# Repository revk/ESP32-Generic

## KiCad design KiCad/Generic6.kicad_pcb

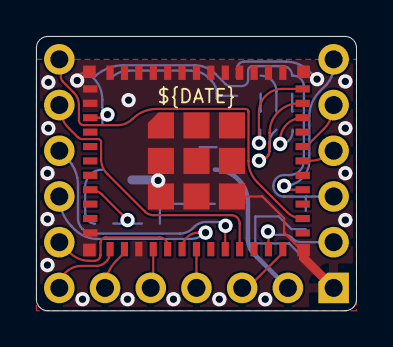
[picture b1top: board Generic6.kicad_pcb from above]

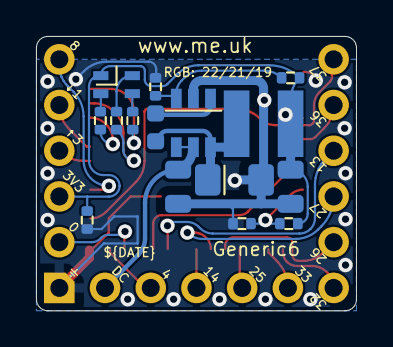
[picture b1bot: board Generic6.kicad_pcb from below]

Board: 2 copper layers, 17.8 x 15.2 mm, 29 parts (28 on the bottom side), 25 nets.

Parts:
C1: 10nF; C_0402
C2: 0.1uF; Hidden
C3: 2.2uF; Hidden
C4: 10uF; Hidden
C5: 100nF; C_0402
D1: RGB; LED-RGB-1.6x1.6
D2: Schottky; Hidden
J1: Shelly
L1: 6.8uH; Hidden
P1: 4; Round
P2: 32; Round
P3: 13; Round
P4: 25; Round
P5: 26; Round
P6: 33; Round
P7: 8; Round
P8: 27; Round
P9: 14; Round
P10: 37; Round
P11: 36; Round
P12: DC; Round
R1: 680R; R_0402
R2: 2K; R_0402
R3: 220R; R_0402
R4: 10K; R_0402
R5: 100k 1% or 0R; R_0402
R6: 30k 1% or NF; R_0402
U1: ESP32-PICO-MINI-02
U2: LMR16006+FB; RegulatorBlockFB

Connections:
+3V3: C5.1, D1.1 (A), J1.3 (3V3), R4.1, R5.1, U1.3 (3V3), U2.4 (VOUT)
B: R3.2, U1.33 (IO19)
EN: C1.2, R4.2, U1.8 (EN)
G: R2.2, U1.35 (IO21)
GND: C1.1, C5.2, J1.1 (GND), R6.1, U1.1 (GND), U1.2 (GND), U1.11 (GND), U1.14 (GND), U1.36 (GND), U1.37 (GND), U1.38 (GND), U1.39 (GND), U1.40 (GND), U1.41 (GND), U1.42 (GND), U1.43 (GND), U1.44 (GND), U1.45 (GND), U1.46 (GND), U1.47 (GND), U1.48 (GND), U1.49 (GND), U1.50 (GND), U1.51 (GND), U1.52 (GND), U1.53 (GND), U2.3 (GND)
unnamed: D1.2 (RK), R1.1
unnamed: D1.3 (GK), R2.1
unnamed: D1.4 (BK), R3.1
unnamed: J1.2 (0), U1.23 (IO0)
unnamed: J1.4 (Rx), U1.30 (RXD0)
unnamed: J1.5 (Tx), U1.31 (TXD0)
unnamed: P1.1, U1.24 (IO4)
unnamed: P2.1, U1.12 (IO32)
unnamed: P3.1, U1.20 (IO13)
unnamed: P4.1, U1.15 (IO25)
unnamed: P5.1, U1.16 (IO26)
unnamed: P6.1, U1.13 (IO33)
unnamed: P7.1, U1.28 (IO8)
unnamed: P8.1, U1.17 (IO27)
unnamed: P9.1, U1.18 (IO14)
unnamed: P12.1, U2.1 (SHDN), U2.2 (VIN)
unnamed: R5.2, R6.2, U2.5 (FB)
unnamed: P11.1, U1.21 (IO15)
unnamed: P10.1, U1.26 (IO20)
R: R1.2, U1.34 (IO22)

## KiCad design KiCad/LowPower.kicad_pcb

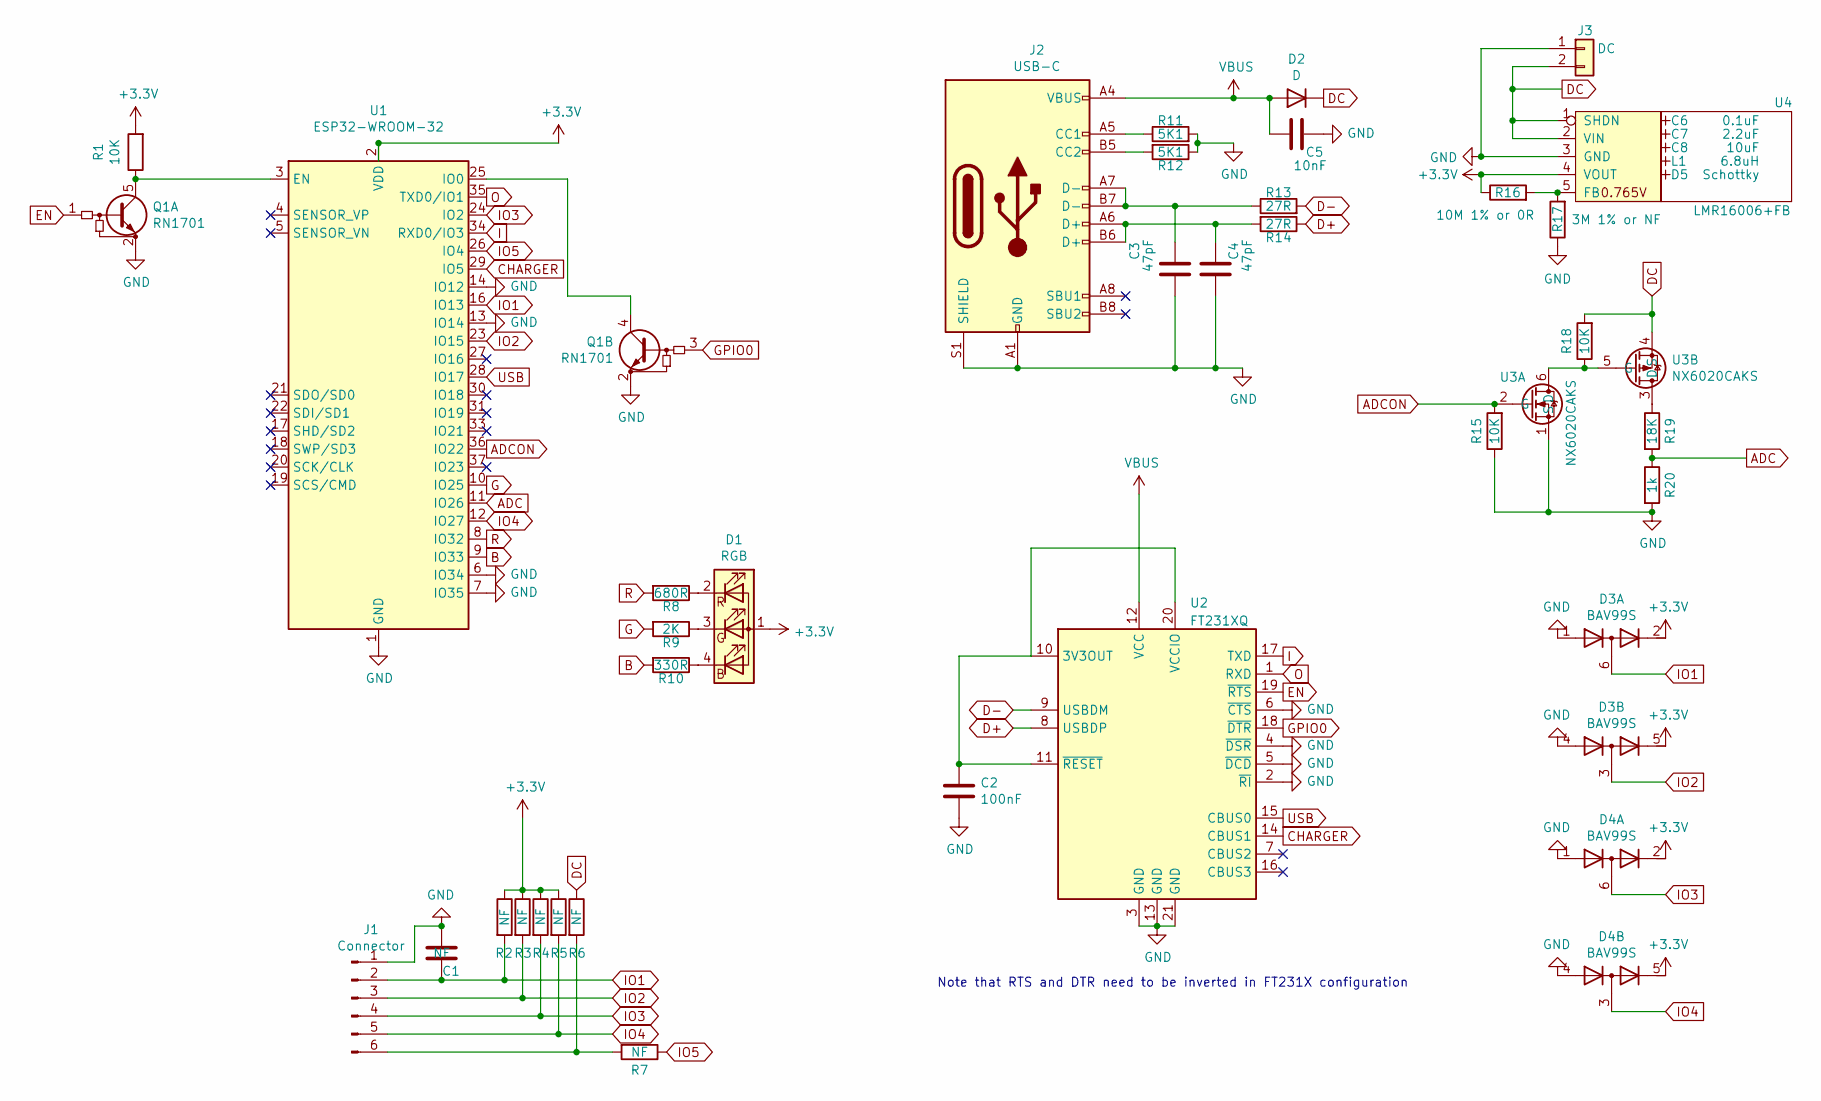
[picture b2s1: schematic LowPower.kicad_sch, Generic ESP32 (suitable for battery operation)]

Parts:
C1: NF; Pad_1206_0805_Open
C2: 100nF; C_0603
C3, C4: 47pF; C_0603
C5: 10nF; C_0603
C6: 0.1uF; Hidden
C7: 2.2uF; Hidden
C8: 10uF; Hidden
D1: RGB; LED-RGB-1.6x1.6; Part No APTF1616LSEEZGKQBKC
D2: D; D_1206_3216Metric
D3, D4: BAV99S; SOT-363_SC-70-6; Part No BAV99S
D5: Schottky; Hidden; Part No CD1206-B2100
J1: Connector; Molex_MiniSPOX_H6RA; Part No 0022057065
J2: USB-C; USC16-TR-Round; Part No CSP-USC16-TR
J3: DC; PinHeader_1x02_P2.54mm_Vertical
L1: 6.8uH; Hidden; Part No TYA4020
Q1: RN1701; USV-5; Part No RN1701
R1, R15: 10K; R_0603
R2, R3, R4, R5, R6, R7: NF; Pad_1206_0805_Open
R8: 680R; R_0603
R9: 2K; R_0603
R10: 330R; R_0603
R11, R12: 5K1; R_0603
R13, R14: 27R; R_0603
R16: 10M 1% or 0R; R_0603
R17: 3M 1% or NF; R_0603
R18: 10K; R_0603; PartNo LMR16006XDDCR
R19: 18K; R_0603
R20: 1k; R_0603
U1: ESP32-WROOM-32; Part No ESP32-WROOM-32
U2: FT231XQ; QFN-20-1EP_4x4mm_P0.5mm_EP2.5x2.5mm
U3: NX6020CAKS; SOT-363_SC-70-6; Part No NX6020CAKS
U4: LMR16006+FB; RegulatorBlockFB; Part No LMR16006YQ3

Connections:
+3V3: D1.1 (A), D3.2 (K2), D3.5 (K4), D4.2 (K2), D4.5 (K4), R1.2, R2.1, R3.1, R4.1, R5.1, R16.1, U1.2 (VDD), U4.4 (VOUT)
ADC: R19.2, R20.1, U1.11 (IO26)
ADCON: R15.2, U1.36 (IO22), U3.2 (G)
B: R10.2, U1.9 (IO33)
CHARGER: U1.29 (IO5), U2.14 (CBUS1)
D+: R14.1, U2.8 (USBDP)
D-: R13.2, U2.9 (USBDM)
DC: D2.1 (K), J3.2, R6.1, R18.2, U3.4 (S), U4.1 (SHDN), U4.2 (VIN)
EN: Q1.1 (B2), U2.19 (~RTS)
G: R9.2, U1.10 (IO25)
GND: C1.1, C2.2, C3.2, C4.2, C5.1, D3.1 (A1), D3.4 (A3), D4.1 (A1), D4.4 (A3), J1.1, J2.A1 (GND), J2.A12 (GND), J2.B1 (GND), J2.B12 (GND), J2.S1 (SHIELD), J3.1, Q1.2 (E), R11.2, R12.1, R15.1, R17.1, R20.2, U1.1 (GND), U1.6 (IO34), U1.7 (IO35), U1.13 (IO14), U1.14 (IO12), U1.15 (GND), U1.38 (GND), U1.39 (GND), U2.2 (~RI), U2.3 (GND), U2.4 (~DSR), U2.5 (~DCD), U2.6 (~CTS), U2.13 (GND), U2.21 (GND), U3.1 (S), U4.3 (GND)
GPIO0: Q1.3 (B2), U2.18 (~DTR)
I: U1.34 (RXD0/IO3), U2.17 (TXD)
IO1: C1.2, D3.6 (K3A4), J1.2, R2.2, U1.16 (IO13)
IO2: D3.3 (K1A2), J1.3, R3.2, U1.23 (IO15)
IO3: D4.6 (K3A4), J1.4, R4.2, U1.24 (IO2)
IO4: D4.3 (K1A2), J1.5, R5.2, U1.12 (IO27)
IO5: R7.1, U1.26 (IO4)
unnamed: C2.1, U2.10 (3V3OUT), U2.11 (~RESET), U2.20 (VCCIO)
unnamed: C3.1, J2.A7 (D-), J2.B7 (D-), R13.1
unnamed: C4.1, J2.A6 (D+), J2.B6 (D+), R14.2
unnamed: D1.2 (RK), R8.1
unnamed: D1.3 (GK), R9.1
unnamed: D1.4 (BK), R10.1
unnamed: J1.6, R6.2, R7.2
unnamed: J2.A5 (CC1), R11.1
unnamed: J2.B5 (CC2), R12.2
unnamed: Q1.4 (C2), U1.25 (IO0)
unnamed: Q1.5 (C2), R1.1, U1.3 (EN)
unnamed: R16.2, R17.2, U4.5 (FB)
unnamed: R18.1, U3.5 (G), U3.6 (D)
unnamed: R19.1, U3.3 (D)
O: U1.35 (TXD0/IO1), U2.1 (RXD)
R: R8.2, U1.8 (IO32)
USB: U1.28 (IO17), U2.15 (CBUS0)
VBUS: C5.2, D2.2 (A), J2.A4 (VBUS), J2.A9 (VBUS), J2.B4 (VBUS), J2.B9 (VBUS), U2.12 (VCC)

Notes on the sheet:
Note that RTS and DTR need to be inverted in FT231X configuration

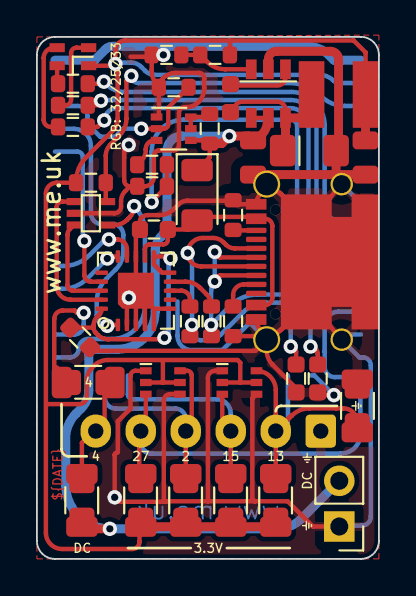
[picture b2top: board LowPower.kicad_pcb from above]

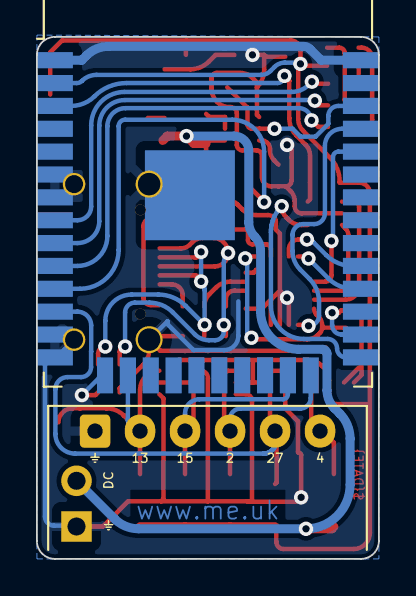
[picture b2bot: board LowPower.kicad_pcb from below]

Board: 2 copper layers, 19.0 x 29.0 mm, 42 parts (2 on the bottom side), 36 nets.

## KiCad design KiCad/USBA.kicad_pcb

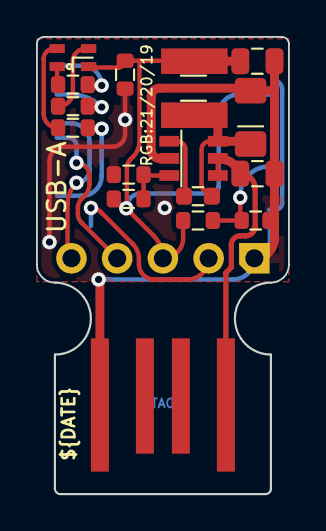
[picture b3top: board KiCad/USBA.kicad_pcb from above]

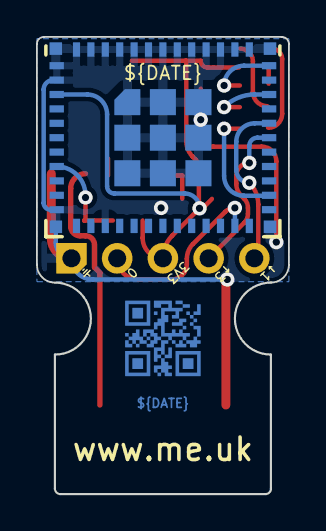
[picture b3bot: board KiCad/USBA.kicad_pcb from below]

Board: 2 copper layers, 14.0 x 25.4 mm, 19 parts (3 on the bottom side), 14 nets.

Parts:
C1: 0.1uF; C_0603_
C2: 2.2uF; C_0805_
C3: 10uF; C_0805_
C4: 100nF; C_0603
C5: 10nF; C_0603
D1: RGB; LED-RGB-1.6x1.6
D2: Schottky; D_1206_
J1: USB_A; USB-A-PCB
J2: Shelly
L1: 6.8uH; L_4x4_
R1: 680R; R_0603
R2: 2K; R_0603
R3: 330R; R_0603
R4: 100k 1% or 0R; R_0603
R5: 30k 1% or NF; R_0603
R6: 10k; R_0603
U1: ESP32-PICO-MINI-02
U2: LMR16006+FB; SOT-23-Thin-6-Reg
U4: QR; QR-GENERIC

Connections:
+3.3V: C4.1, D1.1 (A), J2.3 (3V3), R4.1, R6.1, U1.3 (3V3), U2.4 (VOUT)
B: R3.2, U1.33 (IO19)
EN: C5.2, R6.2, U1.8 (EN)
G: R2.2, U1.26 (IO20)
GND: C4.2, C5.1, J1.4 (GND), J2.1 (GND), R5.1, U1.1 (GND), U1.2 (GND), U1.11 (GND), U1.14 (GND), U1.36 (GND), U1.37 (GND), U1.38 (GND), U1.39 (GND), U1.40 (GND), U1.41 (GND), U1.42 (GND), U1.43 (GND), U1.44 (GND), U1.45 (GND), U1.46 (GND), U1.47 (GND), U1.48 (GND), U1.49 (GND), U1.50 (GND), U1.51 (GND), U1.52 (GND), U1.53 (GND), U2.3 (GND)
GPIO0: J2.2 (0), U1.23 (IO0)
I: J2.4 (Rx), U1.30 (RXD0)
unnamed: D1.2 (RK), R1.1
unnamed: D1.3 (GK), R2.1
unnamed: D1.4 (BK), R3.1
unnamed: R4.2, R5.2, U2.5 (FB)
O: J2.5 (Tx), U1.31 (TXD0)
R: R1.2, U1.35 (IO21)
VBUS: J1.1 (VBUS), U2.1 (SHDN), U2.2 (VIN)

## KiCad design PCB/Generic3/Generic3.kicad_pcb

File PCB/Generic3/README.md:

# Generic3

## Trademark

This is an open source project, but bear in mind you cannot sell boards bearing the Andrews & Arnold Ltd name, the A&A logo, the registered trademark AJK logo, or the GS1 allocated EANs assigned to Andrews & Arnold Ltd.

## PCB Designs

These files are for use with [KiCAD](https://www.kicad.org).

- [Generic3](Generic3.kicad_pro)
## 3D

3D case designs are normally automatically created from the PCB so as to ensure correct details and placement of apertures, etc.

- [Generic3](Generic3.stl)

## Images

---

*Auto generated README.md 2025-08-25T14:29:06*

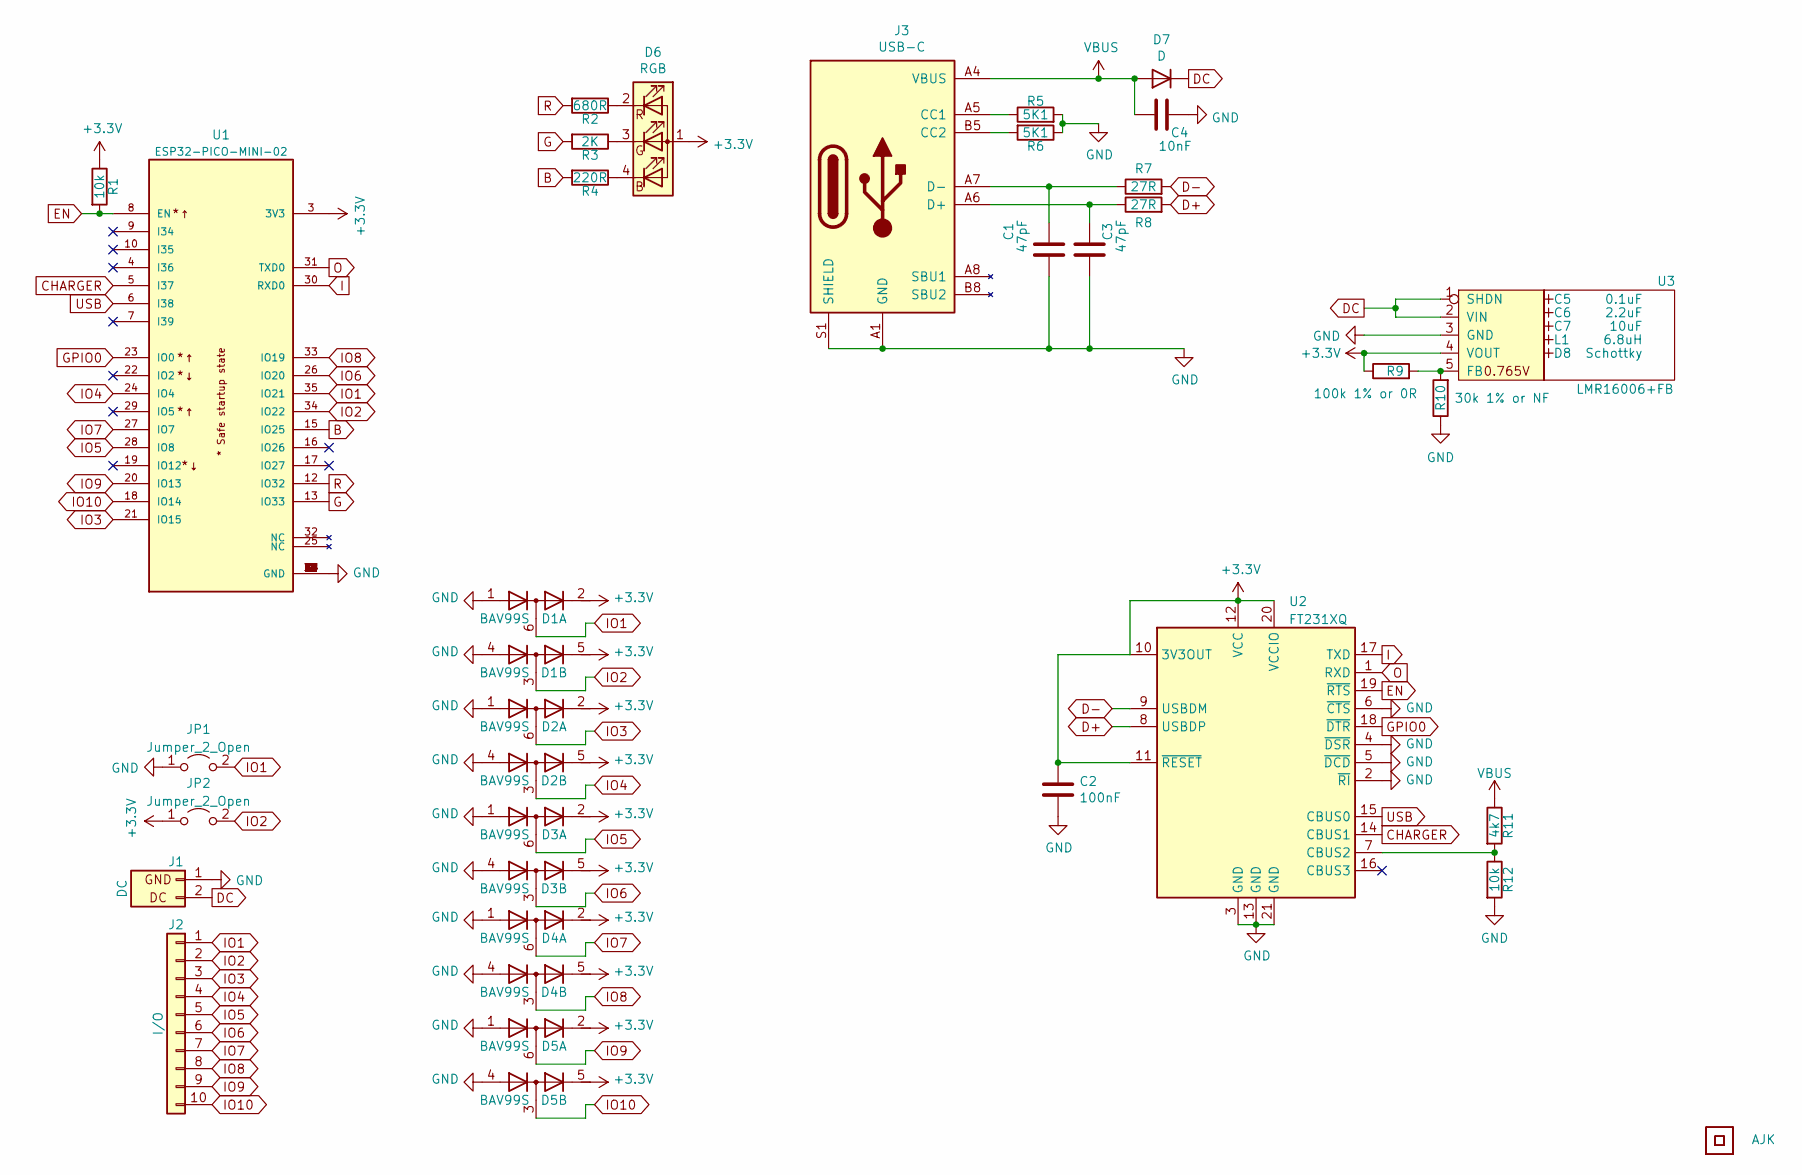
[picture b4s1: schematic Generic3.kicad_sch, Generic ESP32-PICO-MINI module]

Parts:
C1, C3: 47pF; C_0603
C2: 100nF; C_0603
C4: 10nF; C_0603
C5: 0.1uF; Hidden
C6: 2.2uF; Hidden
C7: 10uF; Hidden
D1, D2, D3, D4, D5: BAV99S; SOT-363_SC-70-6
D6: RGB; LED-RGB-1.6x1.6; Part No APTF1616LSEEZGKQBKC
D7: D; D_1206
D8: Schottky; Hidden; Part No CD1206-B2100
J1: DC; Molex_MiniSPOX_H2RA
J2: I/O; Molex_MiniSPOX_H10RA
J3: USB-C; USC16-TR-Round; Part No CSP-USC16-TR
JP1, JP2: Jumper_2_Open; Pad_1206_0805_Open
L1: 6.8uH; Hidden; Part No TYA4020
Logo1: AJK
R1, R12: 10k; R_0603
R2: 680R; R_0603
R3: 2K; R_0603
R4: 220R; R_0603
R5, R6: 5K1; R_0603
R7, R8: 27R; R_0603
R9: 100k 1% or 0R; R_0603
R10: 30k 1% or NF; R_0603
R11: 4k7; R_0603
U1: ESP32-PICO-MINI-02; PARTREV v1.0
U2: FT231XQ; QFN-20-1EP_4x4mm_P0.5mm_EP2.5x2.5mm
U3: LMR16006+FB; RegulatorBlockFB; Part No LMR16006YQ3
U4: QR; QR-GENERIC

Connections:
+3V3: C2.1, D1.2 (K2), D1.5 (K4), D2.2 (K2), D2.5 (K4), D3.2 (K2), D3.5 (K4), D4.2 (K2), D4.5 (K4), D5.2 (K2), D5.5 (K4), D6.1 (A), JP2.1 (A), R1.1, R9.1, U1.3 (3V3), U2.10 (3V3OUT), U2.11 (~RESET), U2.12 (VCC), U2.20 (VCCIO), U3.4 (VOUT)
B: R4.2, U1.15 (IO25)
CHARGER: U1.5 (I37), U2.14 (CBUS1)
D+: R8.2, U2.8 (USBDP)
D-: R7.2, U2.9 (USBDM)
DC: D7.1 (K), J1.2 (DC), U3.1 (SHDN), U3.2 (VIN)
EN: R1.2, U1.8 (EN), U2.19 (~RTS)
G: R3.2, U1.13 (IO33)
GND: C1.2, C2.2, C3.2, C4.1, D1.1 (A1), D1.4 (A3), D2.1 (A1), D2.4 (A3), D3.1 (A1), D3.4 (A3), D4.1 (A1), D4.4 (A3), D5.1 (A1), D5.4 (A3), J1.1 (GND), J3.A1 (GND), J3.A12 (GND), J3.B1 (GND), J3.B12 (GND), J3.S1 (SHIELD), JP1.1 (A), R5.2, R6.1, R10.1, R12.2, U1.1 (GND), U1.2 (GND), U1.11 (GND), U1.14 (GND), U1.36 (GND), U1.37 (GND), U1.38 (GND), U1.39 (GND), U1.40 (GND), U1.41 (GND), U1.42 (GND), U1.43 (GND), U1.44 (GND), U1.45 (GND), U1.46 (GND), U1.47 (GND), U1.48 (GND), U1.49 (GND), U1.50 (GND), U1.51 (GND), U1.52 (GND), U1.53 (GND), U2.2 (~RI), U2.3 (GND), U2.4 (~DSR), U2.5 (~DCD), U2.6 (~CTS), U2.13 (GND), U2.21 (GND), U3.3 (GND)
GPIO0: U1.23 (IO0), U2.18 (~DTR)
I: U1.30 (RXD0), U2.17 (TXD)
IO1: D1.6 (K3A4), J2.1, JP1.2 (B), U1.35 (IO21)
IO2: D1.3 (K1A2), J2.2, JP2.2 (B), U1.34 (IO22)
IO3: D2.6 (K3A4), J2.3, U1.21 (IO15)
IO4: D2.3 (K1A2), J2.4, U1.24 (IO4)
IO5: D3.6 (K3A4), J2.5, U1.28 (IO8)
IO6: D3.3 (K1A2), J2.6, U1.26 (IO20)
IO7: D4.6 (K3A4), J2.7, U1.27 (IO7)
IO8: D4.3 (K1A2), J2.8, U1.33 (IO19)
IO9: D5.6 (K3A4), J2.9, U1.20 (IO13)
IO10: D5.3 (K1A2), J2.10, U1.18 (IO14)
unnamed: C1.1, J3.A7 (D-), J3.B7 (D-), R7.1
unnamed: C3.1, J3.A6 (D+), J3.B6 (D+), R8.1
unnamed: D6.2 (RK), R2.1
unnamed: D6.3 (GK), R3.1
unnamed: D6.4 (BK), R4.1
unnamed: J3.A5 (CC1), R5.1
unnamed: J3.B5 (CC2), R6.2
unnamed: R9.2, R10.2, U3.5 (FB)
unnamed: R11.2, R12.1, U2.7 (CBUS2)
O: U1.31 (TXD0), U2.1 (RXD)
R: R2.2, U1.12 (IO32)
USB: U1.6 (I38), U2.15 (CBUS0)
VBUS: C4.2, D7.2 (A), J3.A4 (VBUS), J3.A9 (VBUS), J3.B4 (VBUS), J3.B9 (VBUS), R11.1

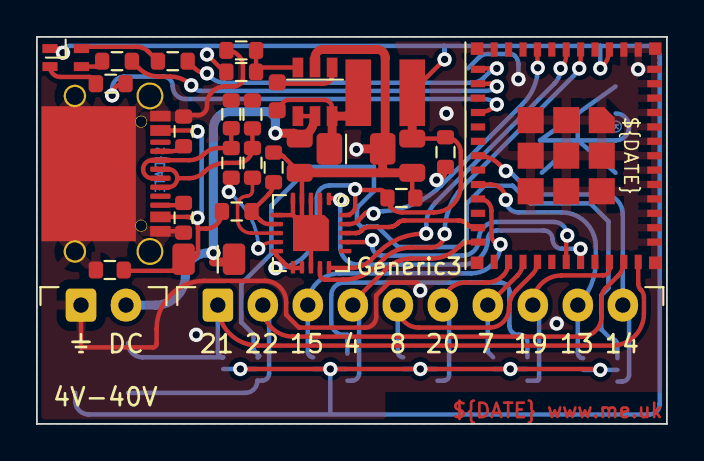
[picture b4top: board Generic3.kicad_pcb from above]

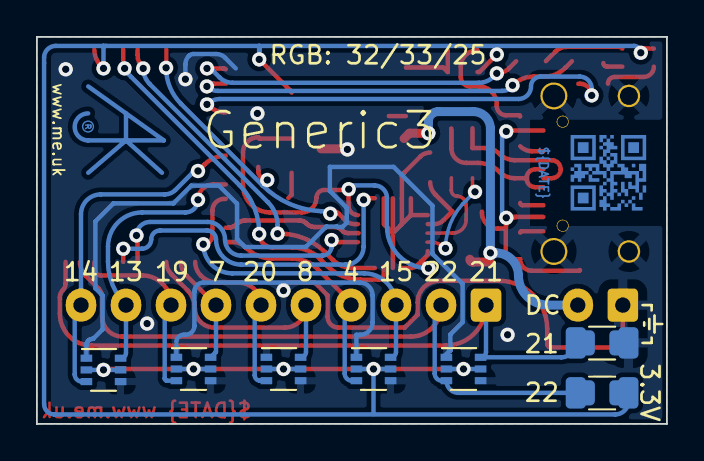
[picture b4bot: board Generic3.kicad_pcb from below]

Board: 2 copper layers, 35.0 x 21.5 mm, 38 parts (9 on the bottom side), 34 nets.

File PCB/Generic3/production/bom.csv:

Designator,Footprint,Quantity,Value,LCSC Part #
"C1, C3",C_0603,2,47pF,
C2,C_0603,1,100nF,
C4,C_0603,1,10nF,
C5,Hidden,1,0.1uF,
C6,Hidden,1,2.2uF,
C7,Hidden,1,10uF,
"D1, D2, D3, D4, D5",SOT-363_SC-70-6,5,BAV99S,
D6,LED-RGB-1.6x1.6,1,RGB,
D7,D_1206,1,D,
D8,Hidden,1,Schottky,
J1,Molex_MiniSPOX_H2RA,1,DC,
J2,Molex_MiniSPOX_H10RA,1,I/O,
J3,USC16-TR-Round,1,USB-C,
L1,Hidden,1,6.8uH,
"R1, R12",R_0603,2,10k,
R10,R_0603,1,30k 1% or NF,
R11,R_0603,1,4k7,
R2,R_0603,1,680R,
R3,R_0603,1,2K,
R4,R_0603,1,220R,
"R5, R6",R_0603,2,5K1,
"R7, R8",R_0603,2,27R,
R9,R_0603,1,100k 1% or 0R,
U1,ESP32-PICO-MINI-02,1,ESP32-PICO-MINI-02,
U2,QFN-20-1EP_4x4mm_P0.5mm_EP2.5x2.5mm,1,FT231XQ,
U3,RegulatorBlockFB,1,LMR16006+FB,

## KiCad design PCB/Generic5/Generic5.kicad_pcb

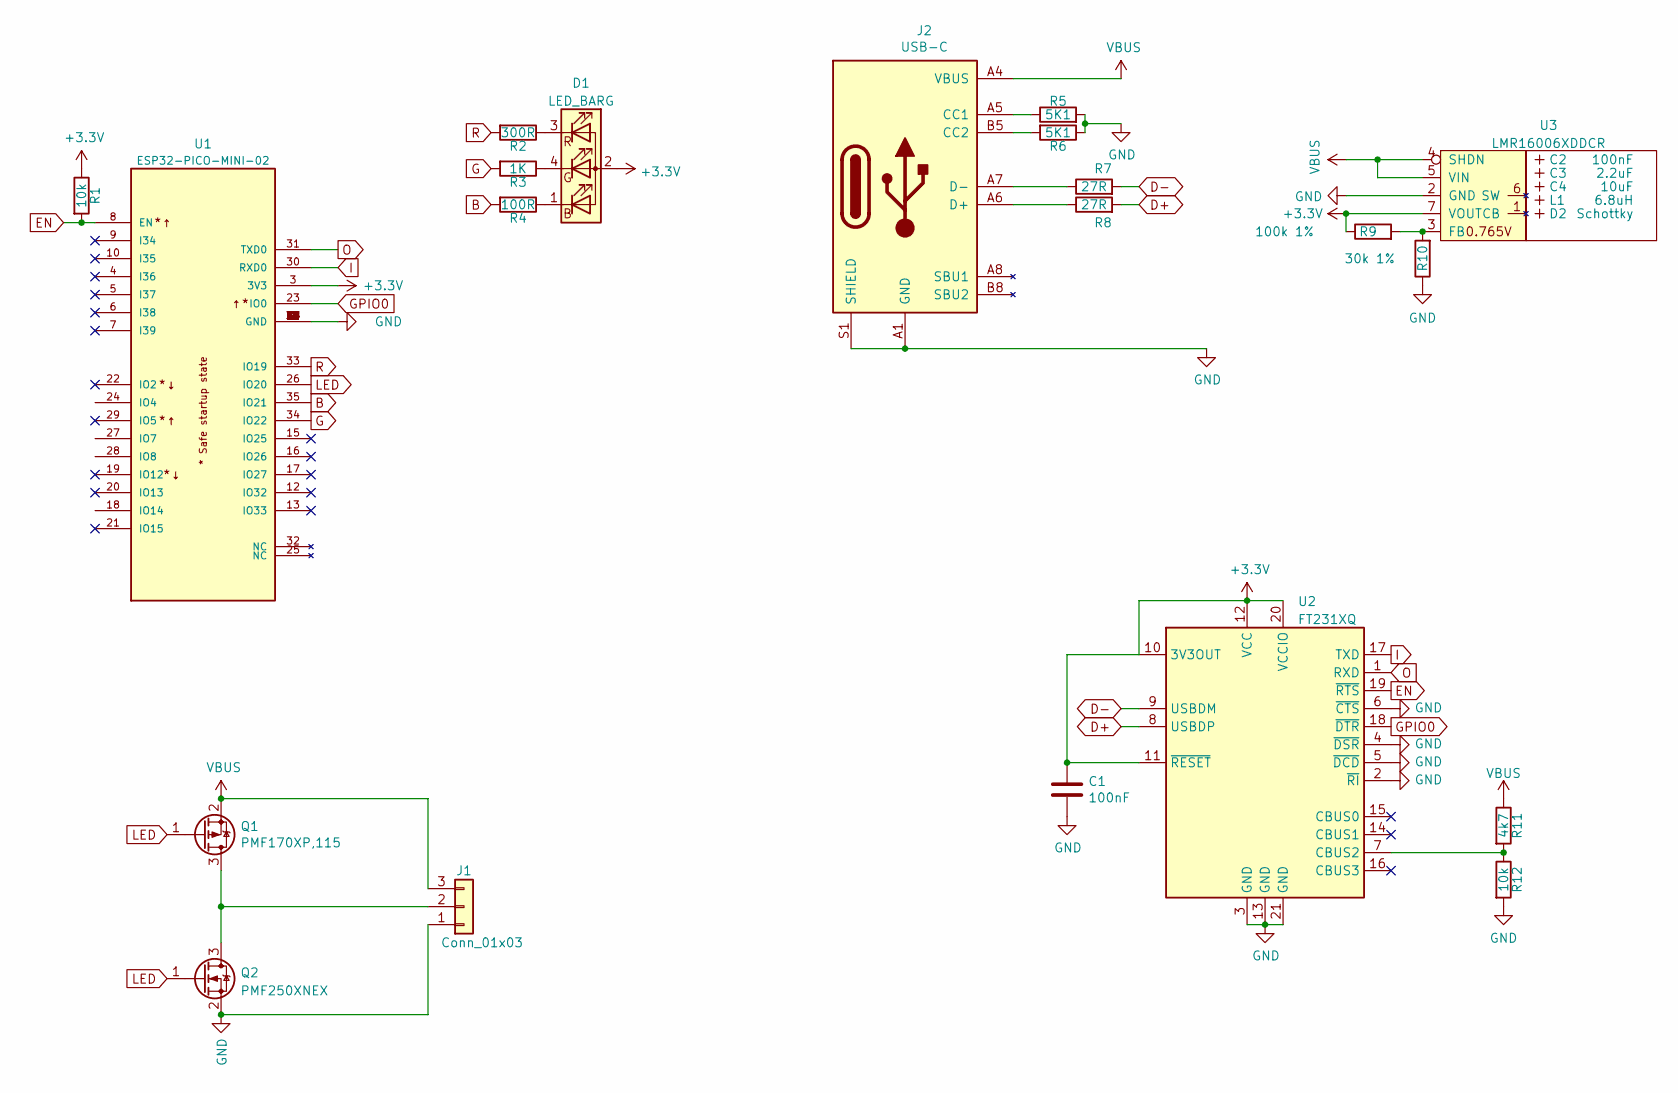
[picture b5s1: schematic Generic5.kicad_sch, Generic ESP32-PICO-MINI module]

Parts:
C1: 100nF; C_0603
C2: 100nF; C_0603_; LCSC Part # C30926
C3: 2.2uF; C_0805_; LCSC Part # C19110
C4: 10uF; C_0805_; LCSC Part # C17024
D1: LED_BARG; MHS190RGBCT; LCSC Part # C409798
D2: Schottky; D_1206_; LCSC Part # C143805
J1: Conn_01x03; PTSM-HH-3-RA
J2: USB-C; USC16-TR-PTH; Part No CSP-USC16-TR
L1: 6.8uH; L_4x4_; LCSC Part # C354575
Q1: PMF170XP,115; SOT-323_SC-70
Q2: PMF250XNEX; SOT-323_SC-70
R1, R12: 10k; R_0603
R2: 300R; R_0603; Part No 0603-680R
R3: 1K; R_0603; Part No 0603-2K
R4: 100R; R_0603; Part No 0603-220R
R5, R6: 5K1; R_0603
R7, R8: 27R; R_0603
R9: 100k 1%; R_0603; LCSC Part # C14675
R10: 30k 1%; R_0603; LCSC Part # C100001
R11: 4k7; R_0603
U1: ESP32-PICO-MINI-02; PARTREV v1.0; LCSC Part # C2980306
U2: FT231XQ; QFN-20-1EP_4x4mm_P0.5mm_EP2.5x2.5mm
U3: LMR16006XDDCR; SOT-23-Thin-6-Reg; Part No LMR16006XDDCR; LCSC Part # C87080

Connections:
+3V3: C1.1, D1.2 (A), R1.1, R9.1, U1.3 (3V3), U2.10 (3V3OUT), U2.11 (~RESET), U2.12 (VCC), U2.20 (VCCIO), U3.7 (VOUT)
B: R4.2, U1.35 (IO21)
D+: R8.2, U2.8 (USBDP)
D-: R7.2, U2.9 (USBDM)
EN: R1.2, U1.8 (EN), U2.19 (~RTS)
G: R3.2, U1.34 (IO22)
GND: C1.2, J1.1, J2.A1 (GND), J2.A12 (GND), J2.B1 (GND), J2.B12 (GND), J2.S1 (SHIELD), Q2.2 (S), R5.2, R6.1, R10.1, R12.2, U1.1 (GND), U1.2 (GND), U1.11 (GND), U1.14 (GND), U1.36 (GND), U1.37 (GND), U1.38 (GND), U1.39 (GND), U1.40 (GND), U1.41 (GND), U1.42 (GND), U1.43 (GND), U1.44 (GND), U1.45 (GND), U1.46 (GND), U1.47 (GND), U1.48 (GND), U1.49 (GND), U1.50 (GND), U1.51 (GND), U1.52 (GND), U1.53 (GND), U2.2 (~RI), U2.3 (GND), U2.4 (~DSR), U2.5 (~DCD), U2.6 (~CTS), U2.13 (GND), U2.21 (GND), U3.2 (GND)
GPIO0: U1.23 (IO0), U2.18 (~DTR)
I: U1.30 (RXD0), U2.17 (TXD)
LED: Q1.1 (G), Q2.1 (G), U1.26 (IO20)
unnamed: D1.1 (BK), R4.1
unnamed: D1.3 (RK), R2.1
unnamed: D1.4 (GK), R3.1
unnamed: J1.2, Q1.3 (D), Q2.3 (D)
unnamed: J2.A5 (CC1), R5.1
unnamed: J2.A6 (D+), J2.B6 (D+), R8.1
unnamed: J2.A7 (D-), J2.B7 (D-), R7.1
unnamed: J2.B5 (CC2), R6.2
unnamed: R9.2, R10.2, U3.3 (FB)
unnamed: R11.2, R12.1, U2.7 (CBUS2)
O: U1.31 (TXD0), U2.1 (RXD)
R: R2.2, U1.33 (IO19)
VBUS: J1.3, J2.A4 (VBUS), J2.A9 (VBUS), J2.B4 (VBUS), J2.B9 (VBUS), Q1.2 (S), R11.1, U3.4 (SHDN), U3.5 (VIN)

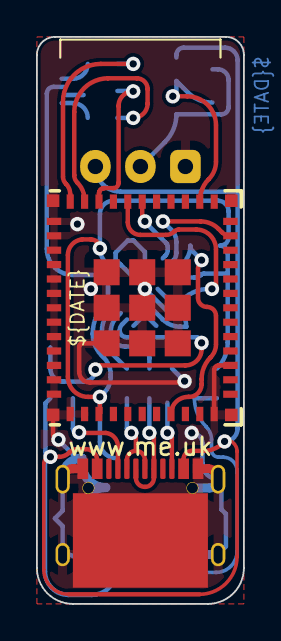
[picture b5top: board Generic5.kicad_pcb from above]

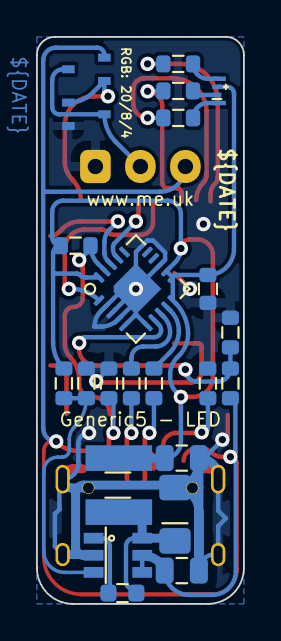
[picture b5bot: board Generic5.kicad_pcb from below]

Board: 2 copper layers, 11.5 x 31.5 mm, 26 parts (23 on the bottom side), 23 nets.

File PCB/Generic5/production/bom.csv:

Designator,Footprint,Quantity,Value,LCSC Part #
C1,C_0603,1,100nF,
C2,C_0603_,1,100nF,C30926
C3,C_0805_,1,2.2uF,C19110
C4,C_0805_,1,10uF,C17024
D1,MHS190RGBCT,1,LED_BARG,C409798
D2,D_1206_,1,Schottky,C143805
J1,PTSM-HH-3-RA,1,Conn_01x03,
J2,USC16-TR-PTH,1,USB-C,
L1,L_4x4_,1,6.8uH,C354575
Q1,SOT-323_SC-70,1,"PMF170XP,115",
Q2,SOT-323_SC-70,1,PMF250XNEX,
"R1, R12",R_0603,2,10k,
R10,R_0603,1,30k 1%,C100001
R11,R_0603,1,4k7,
R2,R_0603,1,300R,
R3,R_0603,1,1K,
R4,R_0603,1,100R,
"R5, R6",R_0603,2,5K1,
"R7, R8",R_0603,2,27R,
R9,R_0603,1,100k 1%,C14675
U1,ESP32-PICO-MINI-02,1,ESP32-PICO-MINI-02,C2980306
U2,QFN-20-1EP_4x4mm_P0.5mm_EP2.5x2.5mm,1,FT231XQ,
U3,SOT-23-Thin-6-Reg,1,LMR16006XDDCR,C87080

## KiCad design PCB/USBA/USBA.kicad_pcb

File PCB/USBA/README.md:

# USBA board

A small PCB design to plug in directly to an old school USB socket for power.
Serial via USB direct to ESP32-S3.

- Includes power supply and WS2812B RGB LED, and then output to drive a chain of such LEDs.
- Includes I2C device (a light sensor) for testing with I2C.
- Includes pads for a button to be fitted to the back.

[Buy](https://www.amazon.co.uk/dp/B0CG3S8JX3) Note some older boards may be simpler RGB LED and env sensor I2C and no button pads.

## Programming

Can be directly programmed using esptool, i.e. `idf.py flash` via the USB headers, or using the 5 pin serial pads on the back of the board.

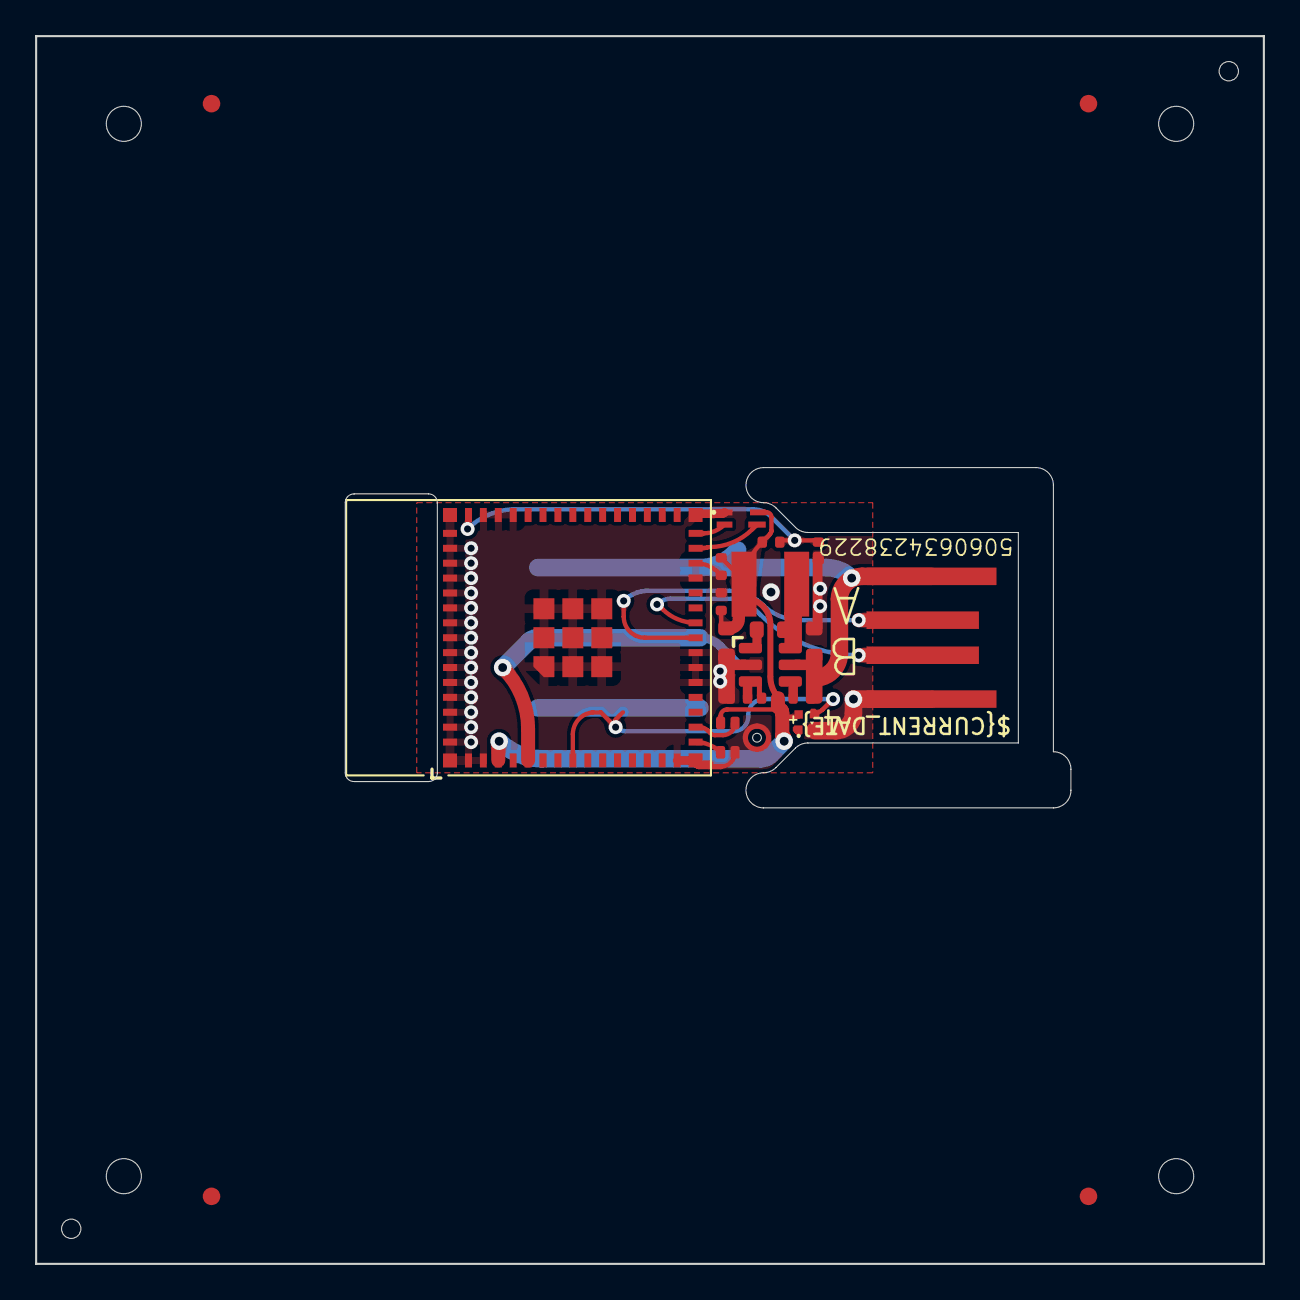
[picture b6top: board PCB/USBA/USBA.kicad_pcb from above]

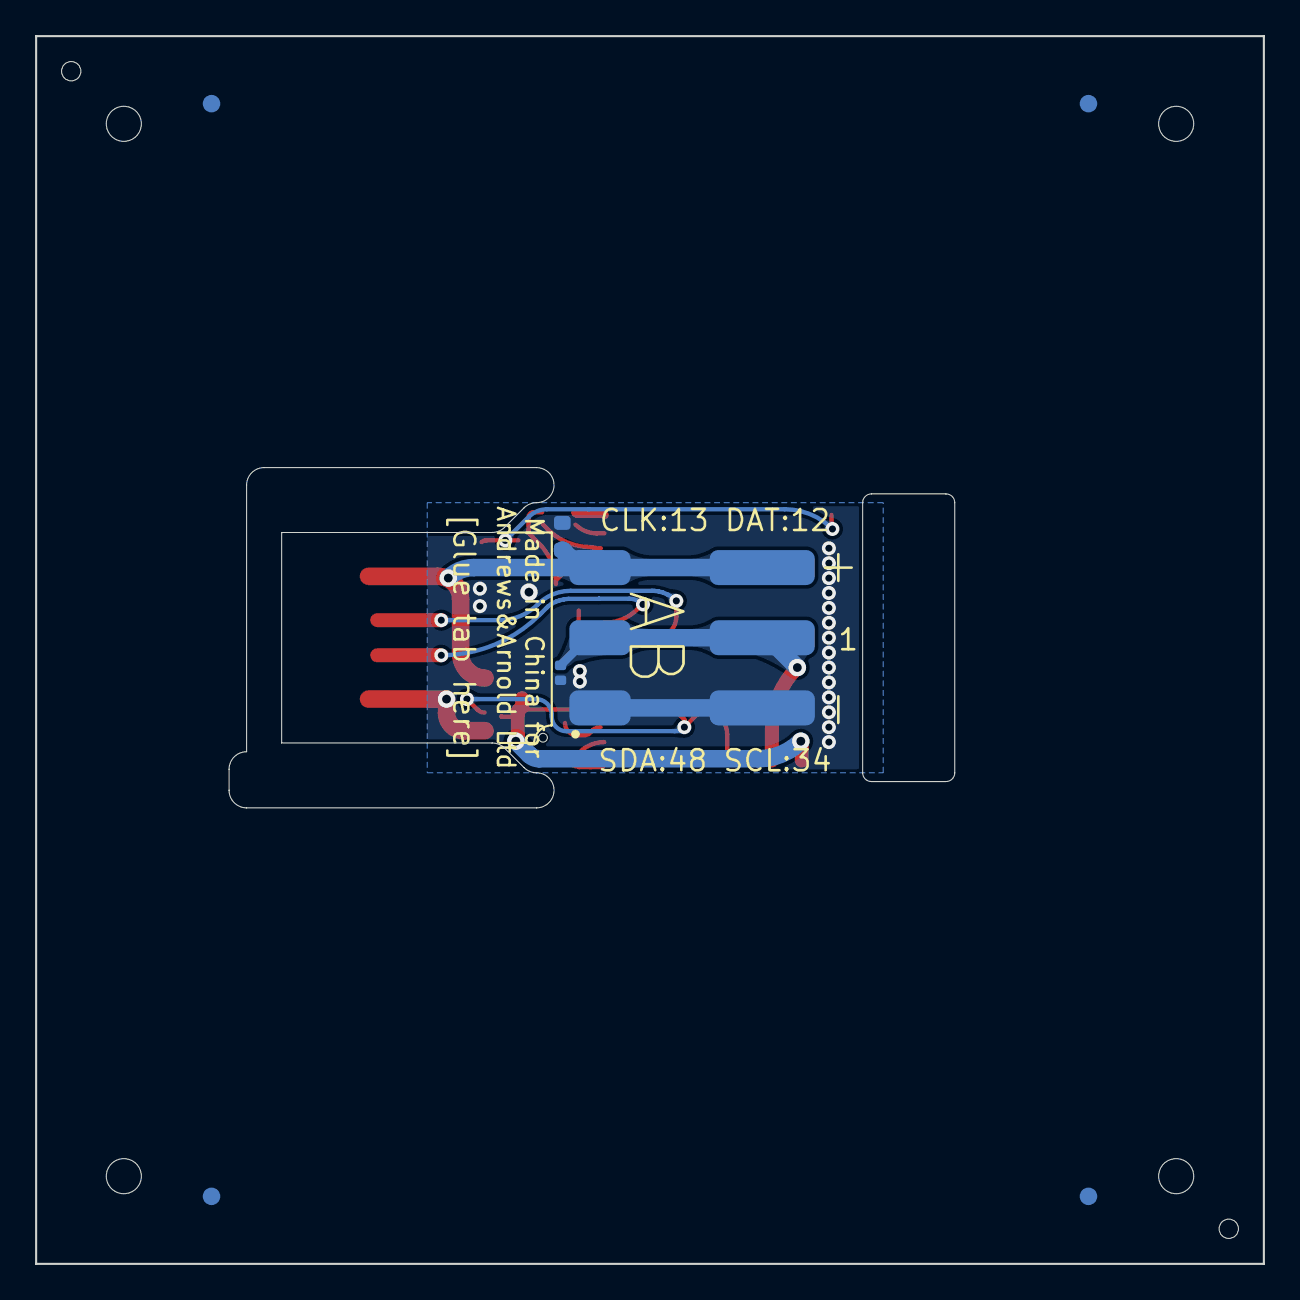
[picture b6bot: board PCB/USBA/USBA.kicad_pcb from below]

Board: 2 copper layers, 70.0 x 70.0 mm, 23 parts (5 on the bottom side), 12 nets.

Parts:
C1: 100nF; C_0402
C2: 22uF; C_0402
C3: 1uF; C_0402
C4: 10uF 35V; C_0603
C6: 10uF 35V; C_0603_
C7: 10uF 6.3V; C_0603_
C8: 100nF; C_0603_
D1: XL-1010RGBC-WS2812B; SMD1010
D2: DFN1006-2L
J1: USB_A; USB-A-PCB
J2: Conn_01x03; WAGO-2060-453-998-404
L2: 10uH; L_4x4_
PCB1: 70x70; PCB7070
R1: 10K; R_0402
R9: 124k; R_0402_
R10: 39k2; R_0402_
R11: 1M; R_0402_
T1: T3902_MEMS_Mic
U1: VEML6040
U2: ESP32-S3-MINI-1
U5: MD8942; SOT-23-6-MD8942
V1, V2: 70; VCUT70N

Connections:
+3.3V: C1.1, C2.1, D1.2 (+), R1.1, T1.5 (VDD), U1.4 (VDD), U2.3 (3V3), U5.8 (VOUT)
CLK: T1.4 (CLK), U2.17 (GPIO13)
D+: J1.3 (D+), U2.24 (GPIO20)
D-: J1.2 (D-), U2.23 (GPIO19)
DATA: T1.1 (DATA), U2.16 (GPIO12)
GND: C1.2, C2.2, C3.2, C4.2, D1.3 (-), D2.1, J1.4 (GND), J2.1, T1.2 (SELECT), T1.3 (GND), U1.1 (GND), U2.1 (GND), U2.2 (GND), U2.15 (GPIO11), U2.20 (GPIO16), U2.21 (GPIO17), U2.22 (GPIO18), U2.27 (GPIO47), U2.28 (GPIO33), U2.42 (GND), U2.43 (GND), U2.44 (GPIO46), U2.46 (GND), U2.47 (GND), U2.48 (GND), U2.49 (GND), U2.50 (GND), U2.51 (GND), U2.52 (GND), U2.53 (GND), U2.54 (GND), U2.55 (GND), U2.56 (GND), U2.57 (GND), U2.58 (GND), U2.59 (GND), U2.60 (GND), U2.61 (GND), U2.62 (GND), U2.63 (GND), U2.64 (GND), U2.65 (GND), U5.2 (GND), U5.7 (GND)
LED1: D1.4 (I), U2.8 (GPIO4)
LED2: D2.2, J2.2, U2.5 (GPIO1)
unnamed: C3.1, R1.2, U2.45 (EN)
SCL: U1.3 (SCL), U2.29 (GPIO34)
SDA: U1.2 (SDA), U2.30 (GPIO48)
VBUS: C4.1, J1.1 (VBUS), J2.3, U5.5 (VIN)

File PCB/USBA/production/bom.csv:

Designator,Footprint,Quantity,Value,LCSC Part #
C1,C_0402,1,100nF,
C2,C_0402,1,22uF,
C3,C_0402,1,1uF,
C4,C_0603,1,10uF 35V,C194427
C6,C_0603_,1,10uF 35V,C194427
C7,C_0603_,1,10uF 6.3V,C1691
C8,C_0603_,1,100nF,
D1,SMD1010,1,XL-1010RGBC-WS2812B,C5349953
D2,DFN1006-2L,1,~,C5137770
J2,WAGO-2060-453-998-404,1,Conn_01x03,C2765056
L2,L_4x4_,1,10uH,
R1,R_0402,1,10K,
R10,R_0402_,1,39k2,
R11,R_0402_,1,1M,
R9,R_0402_,1,124k,
T1,T3902_MEMS_Mic,1,T3902_MEMS_Mic,C3171752
U1,VEML6040,1,VEML6040,C78465
U2,ESP32-S3-MINI-1,1,ESP32-S3-MINI-1,C3013941
U5,SOT-23-6-MD8942,1,MD8942,C2684786
